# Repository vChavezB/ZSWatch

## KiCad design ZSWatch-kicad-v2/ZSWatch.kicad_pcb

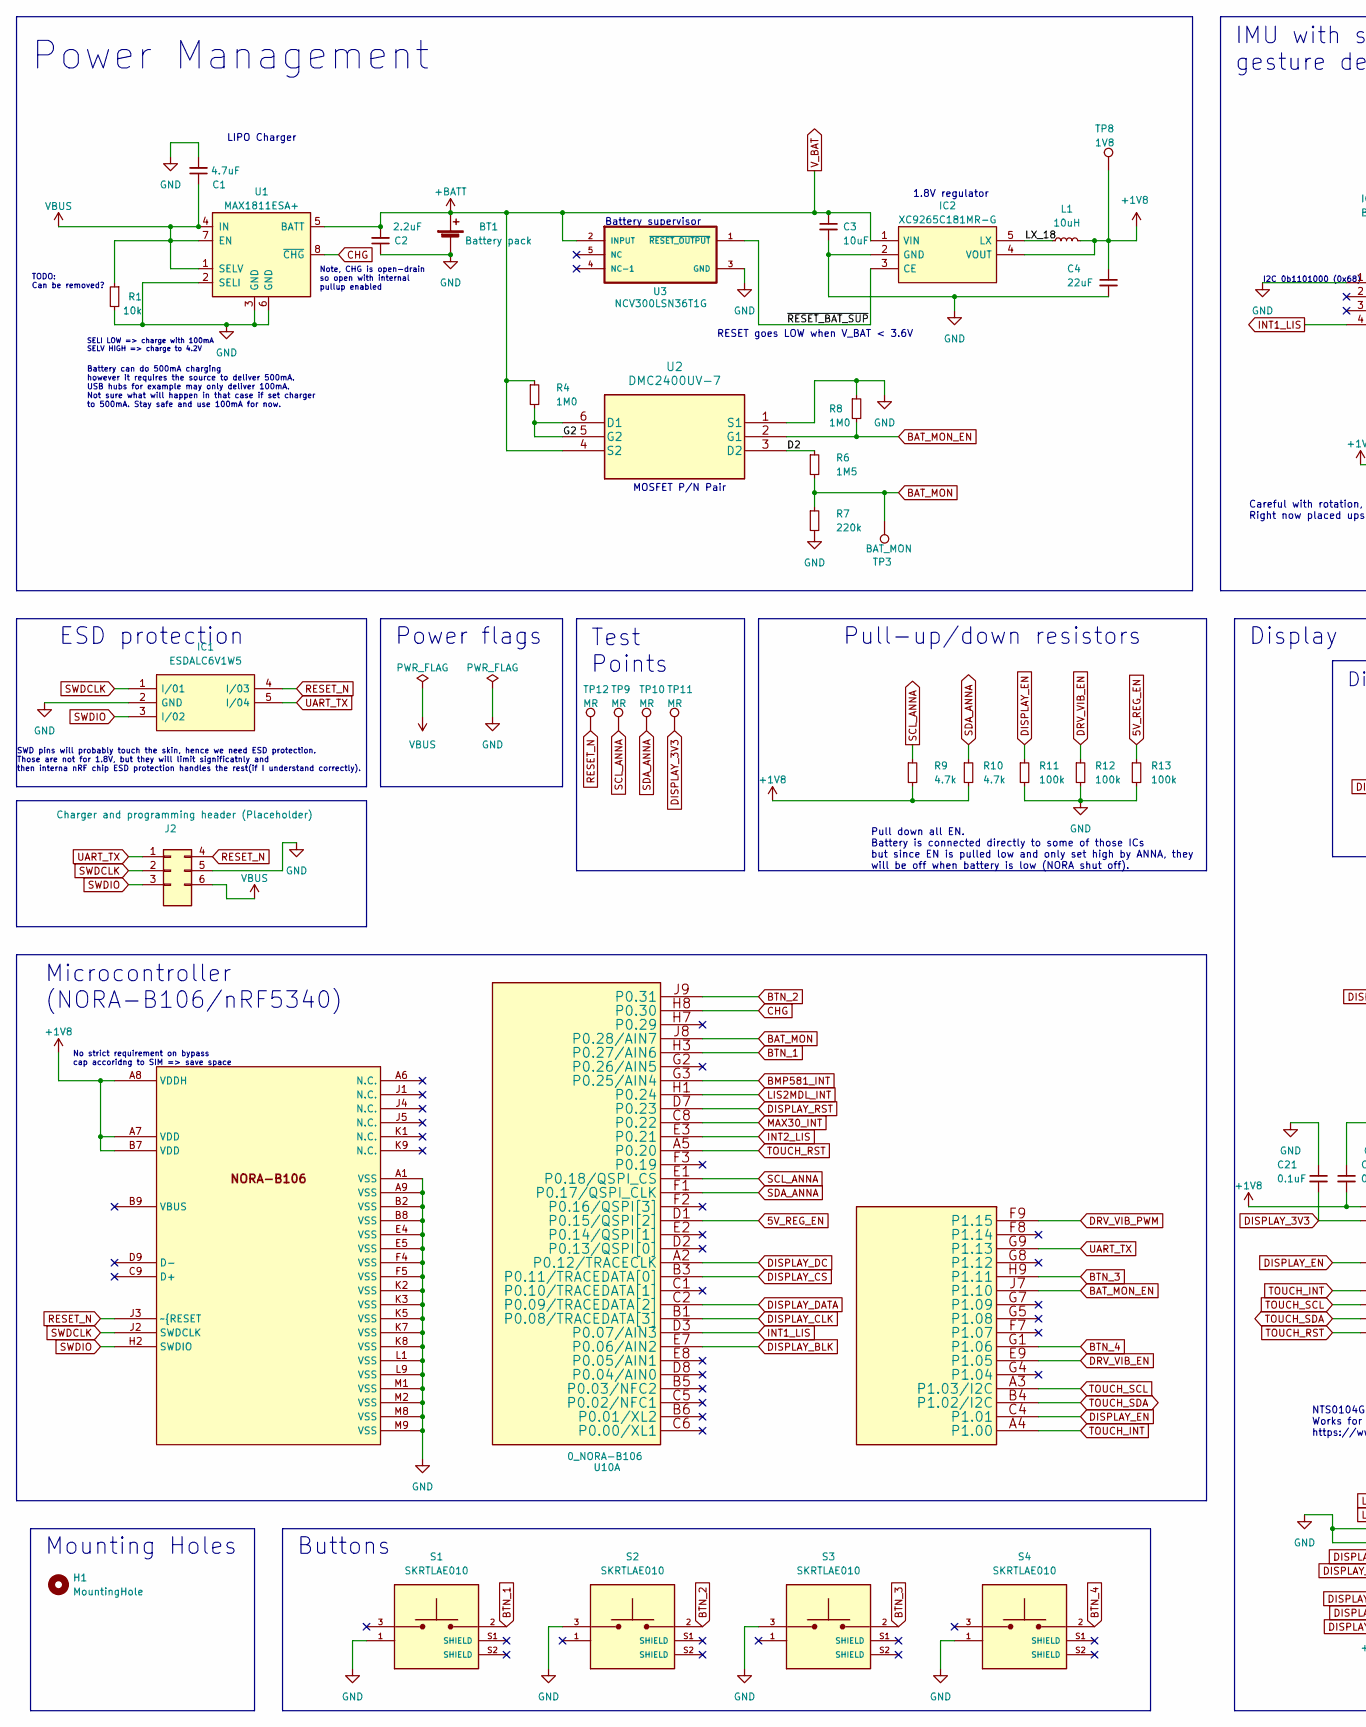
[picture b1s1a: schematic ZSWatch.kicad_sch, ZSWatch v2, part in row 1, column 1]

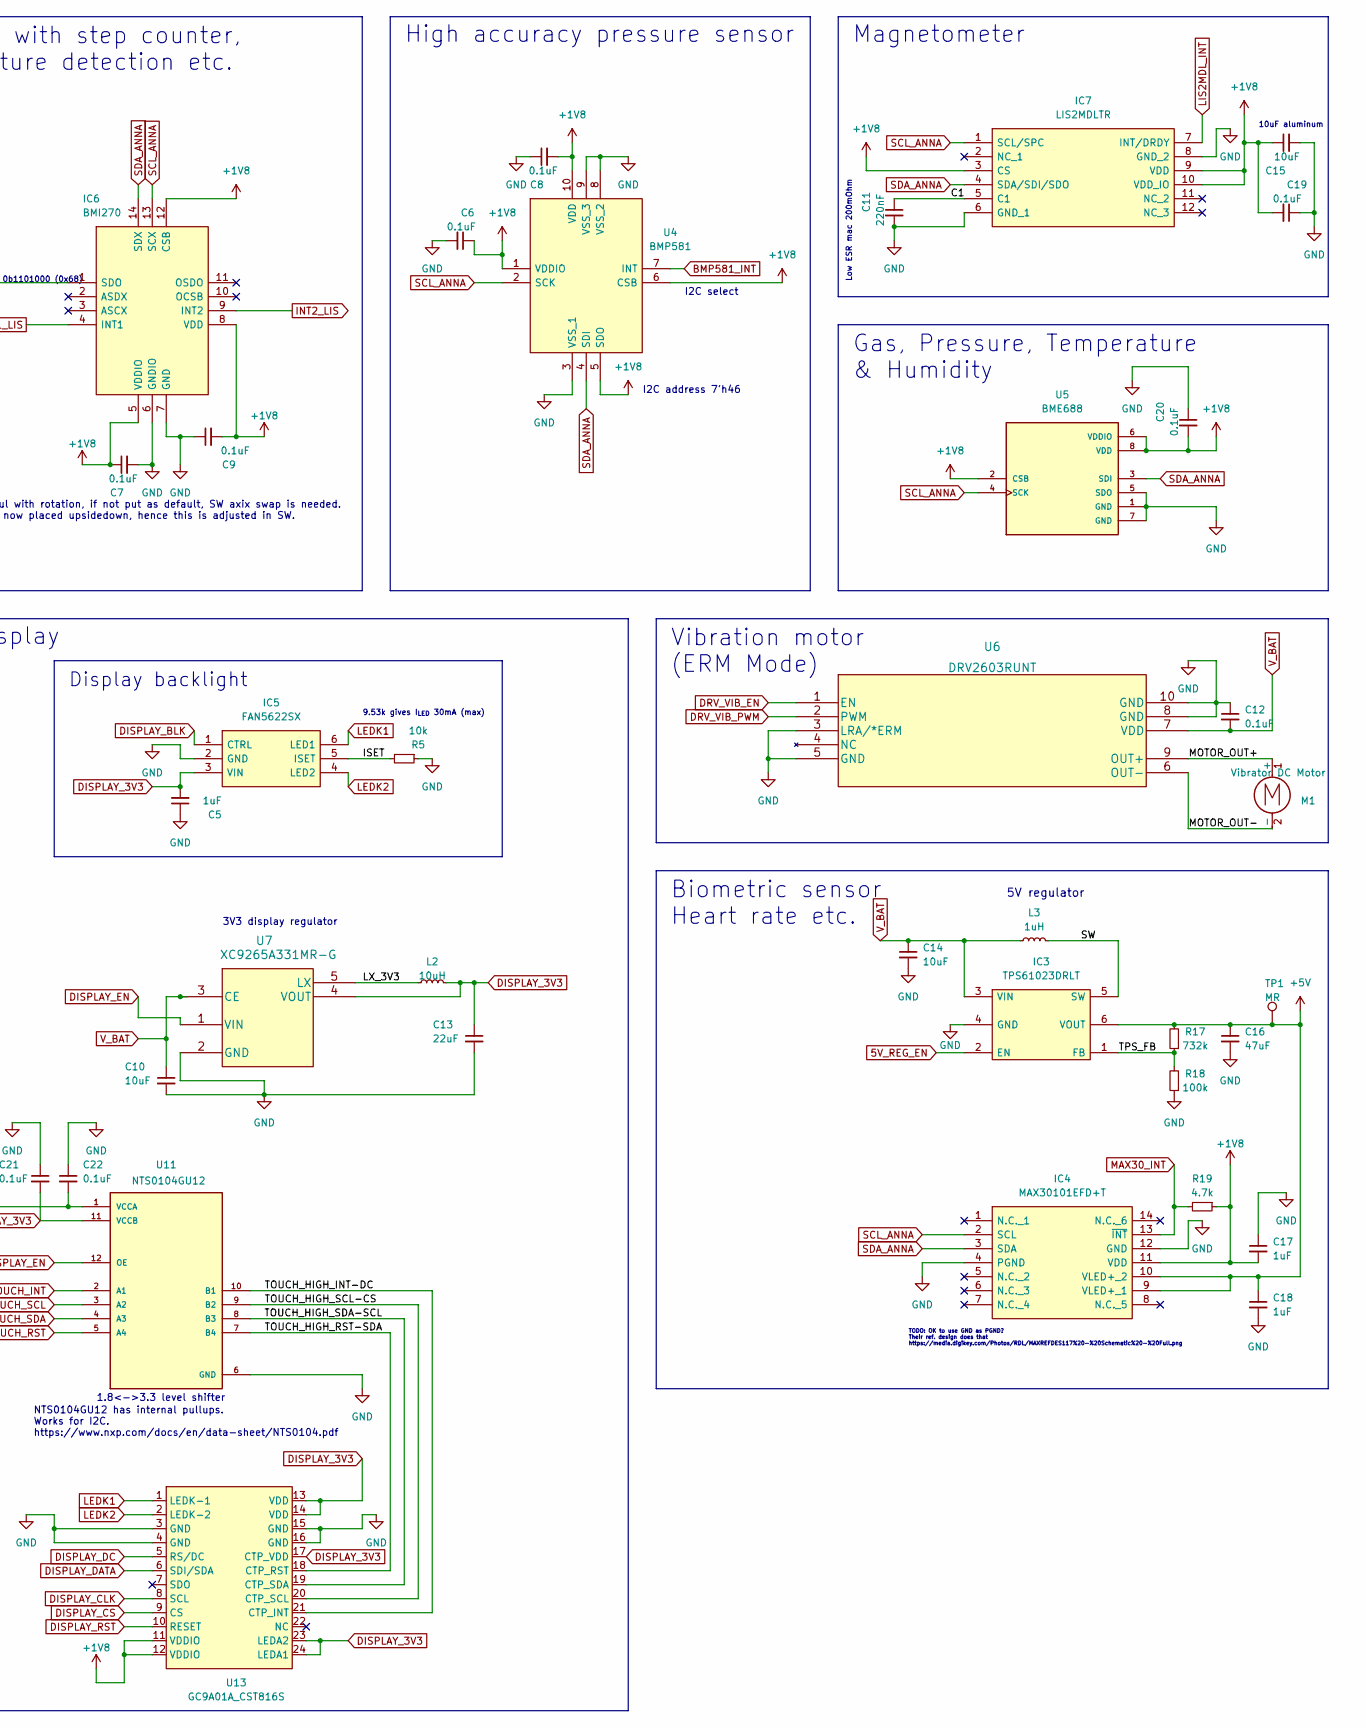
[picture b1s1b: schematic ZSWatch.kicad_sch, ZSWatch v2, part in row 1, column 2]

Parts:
BT1: Battery pack; SolderWire-0.1sqmm_1x02_P3.6mm_D0.4mm_OD1mm
C1: 4.7uF; C_0603_1608Metric
C2: 2.2uF; C_0603_1608Metric
C3, C10, C14, C15: 10uF; C_0603_1608Metric
C4, C13: 22uF; C_0603_1608Metric
C5, C17, C18: 1uF; C_0603_1608Metric
C6, C7, C8, C9, C12, C19, C20, C21, C22: 0.1uF; C_0603_1608Metric
C11: 220nF; C_0603_1608Metric
C16: 47uF; C_0603_1608Metric
H1: MountingHole; MountingHole_3.5mm_Pad_Via
IC1: ESDALC6V1W5; SOT65P210X110-5L; Mouser Part Number 511-ESDALC6V1W5
IC2: XC9265C181MR-G; SOT95P280X130-5N; Mouser Part Number 865-XC9265C181MR-G
IC3: TPS61023DRLT; SOTFL50P160X60-6N; Mouser Part Number 595-TPS61023DRLT
IC4: MAX30101EFD+T; 14-LEAD-OESIP; Mouser Part Number 700-MAX30101EFD+T
IC5: FAN5622SX; SOT95P280X110-6N; Mouser Part Number 512-FAN5622SX
IC6: BMI270; QFN50P300X250X87-14N; Mouser Part Number 262-BMI270
IC7: LIS2MDLTR; LGA-12; Mouser Part Number 511-LIS2MDLTR
J2: Charger and programming header (Placeholder); rtlecs-6-pin-2-54
L1, L2: 10uH; L_0603_1608Metric
L3: 1uH; L_0603_1608Metric
M1: Vibrator DC Motor; TestPoint_2Pads_Pitch2.54mm_Drill0.8mm
R1, R5: 10k; R_0603_1608Metric
R4, R8: 1M0; R_0603_1608Metric
R6: 1M5; R_0603_1608Metric
R7: 220k; R_0603_1608Metric
R9, R10, R19: 4.7k; R_0603_1608Metric
R11, R12, R13, R18: 100k; R_0603_1608Metric
R17: 732k; R_0603_1608Metric
S1, S2, S3, S4: SKRTLAE010; SW_SKRTLAE010; PARTREV --
TP1, TP9, TP10, TP11, TP12: MR; TestPoint_Pad_D1.0mm
TP3: BAT_MON; TestPoint_Pad_D1.0mm
TP8: 1V8; TestPoint_Pad_D1.0mm
U1: MAX1811ESA+; SOIC127P600X175-8N
U2: DMC2400UV-7
U3: NCV300LSN36T1G; SOT95P275X110-5N
U4: BMP581; Mouser Part Number 262-BMP581
U5: BME688; IC_BME688; PARTREV 1.0
U6: DRV2603RUNT
U7: XC9265A331MR-G; SOT95P280X130-5N
U10: 0_NORA-B106; NORA_LGA82R_1430X1040X180_ANT; MANUFACTURER P/N NORA-B106-00B
U11: NTS0104GU12; HPA01164RUTR; PARTREV 4210580/C 06/12
U13: GC9A01A_CST816S; ER-24F24-04

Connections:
5V_REG_EN: IC3.2 (EN), R13.1, U10.D1 (P0.15/QSPI[2])
+1V8: C4.1, C6.1, C7.1, C8.2, C9.2, C15.1, C17.2, C19.2, C20.2, C22.2, IC2.4 (VOUT), IC4.11 (VDD), IC6.5 (VDDIO), IC6.8 (VDD), IC6.12 (CSB), IC7.3 (CS), IC7.9 (VDD), IC7.10 (VDD_IO), L1.2, R9.2, R10.2, R19.1, TP8.1, U4.1 (VDDIO), U4.5 (SDO), U4.6 (CSB), U4.10 (VDD), U5.2 (CSB), U5.6 (VDDIO), U5.8 (VDD), U10.A7 (VDD), U10.A8 (VDDH), U10.B7 (VDD), U11.1 (VCCA), U13.11 (VDDIO), U13.12 (VDDIO)
+5V: C16.1, C18.1, IC3.6 (VOUT), IC4.9 (VLED+_1), IC4.10 (VLED+_2), R17.2, TP1.1
/C1: C11.1, IC7.5 (C1)
/D2: R6.1, U2.3 (D2)
/G2: R4.2, U2.5 (G2), U2.6 (D1)
/ISET: IC5.5 (ISET), R5.2
/LX_3V3: L2.1, U7.5 (LX)
/LX_18: IC2.5 (LX), L1.1
/MOTOR_OUT+: M1.1 (+), U6.9 (OUT+)
/MOTOR_OUT-: M1.2 (-), U6.6 (OUT-)
/SW: IC3.5 (SW), L3.2
/TOUCH_HIGH_INT-DC: U11.10 (B1), U13.21 (CTP_INT)
/TOUCH_HIGH_RST-SDA: U11.7 (B4), U13.18 (CTP_RST)
/TOUCH_HIGH_SCL-CS: U11.9 (B2), U13.20 (CTP_SCL)
/TOUCH_HIGH_SDA-SCL: U11.8 (B3), U13.19 (CTP_SDA)
/TPS_FB: IC3.1 (FB), R17.1, R18.2
/~RESET_BAT_SUP: IC2.3 (CE), U3.1 (~RESET_OUTPUT)
BAT_MON: R6.2, R7.1, TP3.1, U10.J8 (P0.28/AIN7)
BAT_MON_EN: R8.2, U2.2 (G1), U10.J7 (P1.10)
BMP581_INT: U4.7 (INT), U10.G3 (P0.25/AIN4)
BTN_1: S1.2, U10.H3 (P0.27/AIN6)
BTN_2: S2.2, U10.J9 (P0.31)
BTN_3: S3.2, U10.H9 (P1.11)
BTN_4: S4.2, U10.G1 (P1.06)
CHG: U1.8 (~CHG), U10.H8 (P0.30)
DISPLAY_3V3: C5.2, C13.1, C21.2, IC5.3 (VIN), L2.2, TP11.1, U7.4 (VOUT), U11.11 (VCCB), U13.13 (VDD), U13.14 (VDD), U13.17 (CTP_VDD), U13.23 (LEDA2), U13.24 (LEDA1)
DISPLAY_BLK: IC5.1 (CTRL), U10.E7 (P0.06/AIN2)
DISPLAY_CLK: U10.B1 (P0.08/TRACEDATA[3]), U13.8 (SCL)
DISPLAY_CS: U10.B3 (P0.11/TRACEDATA[0]), U13.9 (CS)
DISPLAY_DATA: U10.C2 (P0.09/TRACEDATA[2]), U13.6 (SDI/SDA)
DISPLAY_DC: U10.A2 (P0.12/TRACECLK), U13.5 (RS/DC)
DISPLAY_RST: U10.D7 (P0.23), U13.10 (RESET)
DRV_VIB_EN: R12.1, U6.1 (EN), U10.E9 (P1.05)
DRV_VIB_PWM: U6.2 (PWM), U10.F9 (P1.15)
GND: BT1.2 (-), C1.2, C2.1, C3.2, C4.2, C5.1, C6.2, C7.2, C8.1, C9.1, C10.2, C11.2, C12.1, C13.2, C14.2, C15.2, C16.2, C17.1, C18.2, C19.1, C20.1, C21.1, C22.1, IC1.2 (GND), IC2.2 (GND), IC3.4 (GND), IC4.4 (PGND), IC4.12 (GND), IC5.2 (GND), IC6.1 (SDO), IC6.6 (GNDIO), IC6.7 (GND), IC7.6 (GND_1), IC7.8 (GND_2), J2.5, R1.2, R5.1, R7.2, R8.1, R11.2, R12.2, R13.2, R18.1, S1.1, S2.3, S3.3, S4.1, U1.2 (SELI), U1.3 (GND), U1.6 (GND), U2.1 (S1), U3.3 (GND), U4.3 (VSS_1), U4.8 (VSS_2), U4.9 (VSS_3), U5.1 (GND), U5.5 (SDO), U5.7 (GND), U6.3 (LRA/*ERM), U6.5 (GND), U6.8 (GND), U6.10 (GND), U7.2 (GND), U10.A1 (VSS), U10.A9 (VSS), U10.B2 (VSS), U10.B8 (VSS), U10.E4 (VSS), U10.E5 (VSS), U10.F4 (VSS), U10.F5 (VSS), U10.K2 (VSS), U10.K3 (VSS), U10.K5 (VSS), U10.K7 (VSS), U10.K8 (VSS), U10.L1 (VSS), U10.L9 (VSS), U10.M1 (VSS), U10.M2 (VSS), U10.M8 (VSS), U10.M9 (VSS), U11.6 (GND), U13.3 (GND), U13.4 (GND), U13.15 (GND), U13.16 (GND)
INT1_LIS: IC6.4 (INT1), U10.D3 (P0.07/AIN3)
INT2_LIS: IC6.9 (INT2), U10.E3 (P0.21)
LEDK1: IC5.6 (LED1), U13.1 (LEDK-1)
LEDK2: IC5.4 (LED2), U13.2 (LEDK-2)
LIS2MDL_INT: IC7.7 (INT/DRDY), U10.H1 (P0.24)
MAX30_INT: IC4.13 (~INT), R19.2, U10.C8 (P0.22)
RESET_N: IC1.4 (I/03), J2.4, TP12.1, U10.J3 (~{RESET)
SCL_ANNA: IC4.2 (SCL), IC6.13 (SCX), IC7.1 (SCL/SPC), R9.1, TP9.1, U4.2 (SCK), U5.4 (SCK), U10.E1 (P0.18/QSPI_CS)
SDA_ANNA: IC4.3 (SDA), IC6.14 (SDX), IC7.4 (SDA/SDI/SDO), R10.1, TP10.1, U4.4 (SDI), U5.3 (SDI), U10.F1 (P0.17/QSPI_CLK)
SWDCLK: IC1.1 (I/01), J2.2, U10.J2 (SWDCLK)
SWDIO: IC1.3 (I/02), J2.3, U10.H2 (SWDIO)
TOUCH_INT: U10.A4 (P1.00), U11.2 (A1)
TOUCH_RST: U10.A5 (P0.20), U11.5 (A4)
TOUCH_SCL: U10.A3 (P1.03/I2C), U11.3 (A2)
TOUCH_SDA: U10.B4 (P1.02/I2C), U11.4 (A3)
UART_TX: IC1.5 (I/04), J2.1, U10.G9 (P1.13)
VBUS: C1.1, J2.6, R1.1, U1.1 (SELV), U1.4 (IN), U1.7 (EN)

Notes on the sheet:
Test Points
Display backlight
Battery can do 500mA charging however it requires the source to deliver 500mA. USB hubs for example may only deliver 100mA. Not sure what will happen in that case if set charger to 500mA. Stay safe and use 100mA for now.
1.8<->3.3 level shifter
I2C select
Biometric sensor Heart rate etc.
Gas, Pressure, Temperature & Humidity
High accuracy pressure sensor
3V3 display regulator
Pull-up/down resistors
MOSFET P/N Pair
Power Management
SELI LOW => charge with 100mA SELV HIGH => charge to 4.2V
Battery supervisor
RESET goes LOW when V_BAT < 3.6V
I2C address 7'h46
Low ESR mac 200mOhm
_{I2C 0b1101000 (0x68)}
NTS0104GU12 has internal pullups. Works for I2C. https://www.nxp.com/docs/en/data-sheet/NTS0104.pdf
TODO: Can be removed?
Buttons
Microcontroller (NORA-B106/nRF5340)
TODO: OK to use GND as PGND? Their ref. design does that https://media.digikey.com/Photos/RDL/MAXREFDES117%20-%20Schematic%20-%20Full.png
Note, CHG is open-drain so open with internal pullup enabled
No strict requirement on bypass cap accoridng to SIM => save space
Power flags
9.53k gives I_{LED} 30mA (max)
Magnetometer
SWD pins will probably touch the skin, hence we need ESD protection. Those are not for 1.8V, but they will limit significatnly and then interna nRF chip ESD protection handles the rest(if I understand correctly).
Pull down all EN. Battery is connected directly to some of those ICs but since EN is pulled low and only set high by ANNA, they will be off when battery is low (NORA shut off).
Careful with rotation, if not put as default, SW axix swap is needed. Right now placed upsidedown, hence this is adjusted in SW.
IMU with step counter, gesture detection etc.
LIPO Charger
5V regulator
ESD protection
Vibration motor (ERM Mode)
Mounting Holes
Display
10uF aluminum
1.8V regulator

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
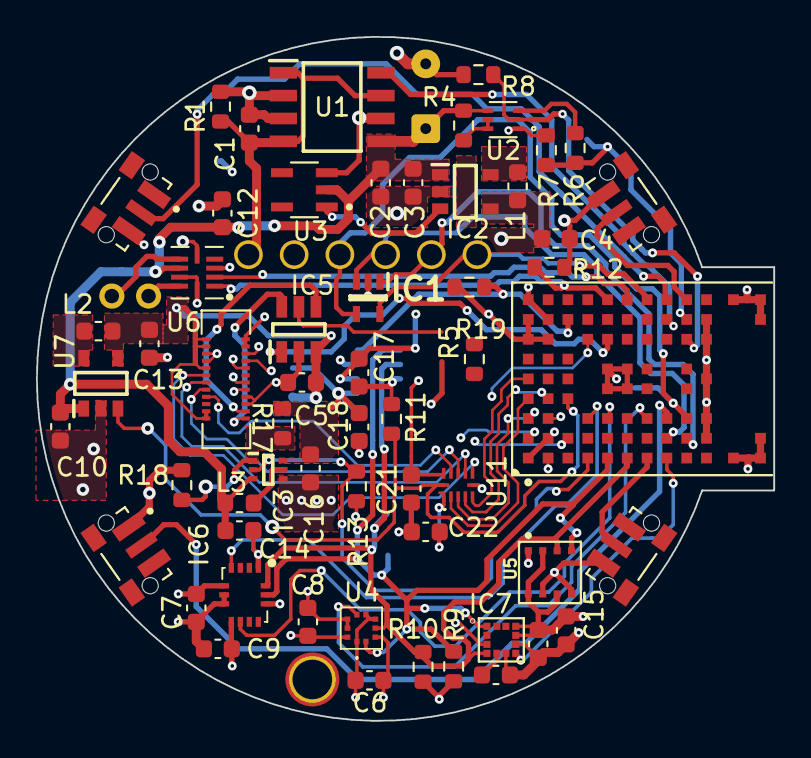
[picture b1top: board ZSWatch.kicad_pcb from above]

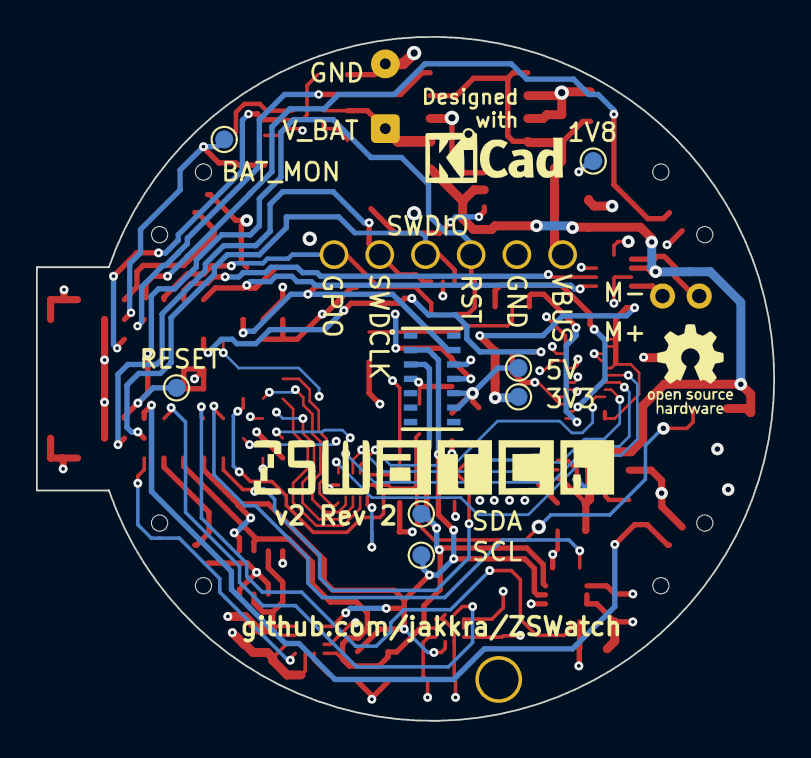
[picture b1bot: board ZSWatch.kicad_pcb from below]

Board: 4 copper layers, 41.0 x 38.0 mm, 70 parts (9 on the bottom side), 55 nets.

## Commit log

2023-07-20 Initial hardware changes to add an external flash (AT25SL128A) to ZSwatch.
2023-07-28 Updated flash pcb design, with DRC rule fixes.
    - Lowered down silkscreen of ZWatch to add test points to SPI for testing.
    - Ground pad of flash is connected but is not necessary and can be removed
    to simplify connections.
    - Due to size constraints added 0402 resistors for pull up resistors on the left side
    of the flash.
    - Pending, change name of FLASH in Kicad to AT25SL128A.
2023-07-29 Added DFU with MCUBoot and external flash
    - This change adds support for the MCUBootloader with
    the external flash AT25SL128A. The spi nor flash driver
    has been activated, configuration for MCUMgr and the
    BT SMP transport for DFU have been activated.
    - Overlay for MCUBoot child image and proper configuration for
    net core have been also included.
2023-07-30 PCB: Tidy up some traces and vias for external flash feature.
2023-07-30 PCB: Move draft flash schematic into its own section. Correct datasheet and model number of flash.
2023-07-31 Added workflow to build kicad diff pdf
    Workflo to build pdf of schematic and pcb with differences on pull request events.
2023-07-31 improved rules for kicad diff ci workflow
2023-07-31 deleted: kibot.yaml
2023-07-31 Inreased DFU speed with MCUMgr
    Added CONFIG_MCUMGR_TRANSPORT_BT_CONN_PARAM_CONTROL to control
    automatically speed of ble connection when SMP is active.
    In addition a patch suggested here was added
    https://github.com/jakkra/ZSWatch/pull/26#issuecomment-1656933604
2023-07-31 Attempt to use NRF5340 DK with Flash
    Currently not working and when main is started
    the app crashes and the bootloader starts again.
2023-07-31 PCB: Fix and exclude DRC errors/warnings we don't care about. Some introduced by moving to KiCad 7.
2023-07-31 Added support for minimal github actions - DRC check - Kicad diff - Build
2023-08-01 Added conditional compilation of DFU if not a posix board.
2023-08-01 Don't unconditionally compile all .c files in src folder. Allow exclusion.
    Don't add dfu when compiling for native_posix.
2023-08-01 Use board revisions to handle external flash.
2023-08-02 Added board revisions for ci build
2023-08-02 Added regex to find board number in CMake
2023-08-23 Added initial commi to test bme688
2023-12-01 test differences

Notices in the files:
parts and their libraries:
Copyright 2021 Accelerated Designs. All rights reserved.
